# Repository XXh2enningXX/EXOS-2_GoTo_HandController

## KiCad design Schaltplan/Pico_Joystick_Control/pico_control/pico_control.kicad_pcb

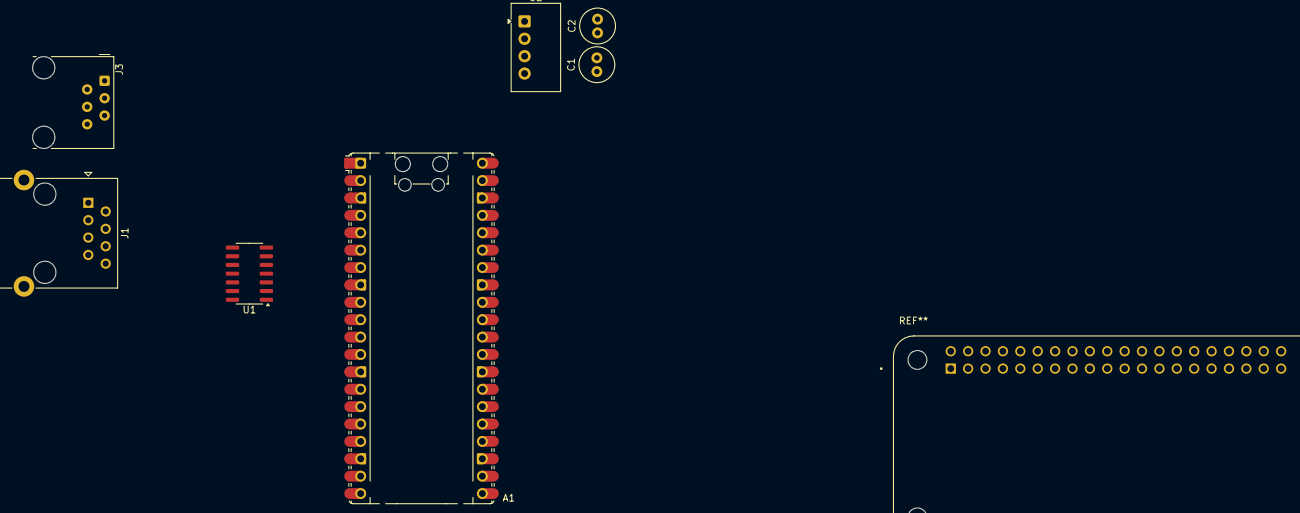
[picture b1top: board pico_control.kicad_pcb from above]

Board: 2 copper layers, 7 parts (0 on the bottom side), 15 nets, no tracks yet.

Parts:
A1: RaspberryPi_Pico; RaspberryPi_Pico_Common_Unspecified
C1, C2: C_Polarized; C_Radial_D5.0mm_H11.0mm_P2.00mm
J1: RJ45; RJ45_Ninigi_GE
J3: RJ12; RJ12_Amphenol_54601-x06_Horizontal
U1: TXB0104D; SOIC-14_3.9x8.7mm_P1.27mm
U2: TBA1-1211; Converter_DCDC_TRACO_TBA1-xxxx_THT

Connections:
+3.3V: A1.36 (3V3), U1.1 (VCCA)
+5V: A1.40 (VBUS), C1.1, U1.14 (VCCB), U2.4 (+Vout)
+12V: C2.1, J1.1, J1.2, U2.2 (+Vin)
GND: A1.3 (GND), A1.8 (GND), A1.13 (GND), A1.18 (GND), A1.23 (GND), A1.28 (GND), A1.38 (GND), C1.2, C2.2, J1.7, J1.8, U1.7 (GND), U2.1 (-Vin), U2.3 (-Vout)
unnamed: A1.35 (ADC_VREF), J3.1
unnamed: A1.33 (AGND), J3.5, J3.6
unnamed: A1.11 (GPIO8), U1.4 (A3)
unnamed: A1.12 (GPIO9), U1.3 (A2)
unnamed: A1.29 (GPIO22), J3.4
unnamed: A1.31 (GPIO26_ADC0), J3.2
unnamed: A1.32 (GPIO27_ADC1), J3.3
unnamed: J1.3, U1.13 (B1)
unnamed: J1.4, U1.12 (B2)
unnamed: J1.5, U1.11 (B3)
unnamed: J1.6, U1.10 (B4)

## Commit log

2025-04-17 Minimal Firmware, nur MNotorsteuerung und Tracking
2025-04-18 Menu angefangen. Muss noch Kompiliert werden und kann dann getestet werden.
2025-04-22 added manual for mount and flashing
2025-04-22 measurement of motor ctrl
2025-04-22 started lite controler version.
2025-04-23 included hex file
2025-04-23 still tryieng to compile
2025-04-23 für GPT
2025-04-23 FreeRTOS comiler works now
2025-04-24 work goes on
2025-04-24 found microcontroler on motor board, PIC16F690, Datasheet added
2025-04-24 started signal analyse
2025-04-25 Analyse der Motorsteuerung
2025-04-29 python signal check
2025-07-17 logic analyser files to csv
2025-07-17 fixed merg issues
2025-09-01 skyvision schematics angefangen
2025-09-01 skyvision board weitere verkabelung vermessen.
2025-09-01 started sorting out schematics
2025-09-01 marked pic pdf
2025-09-01 wip sortieren
2025-09-02 Schaltplan aufgeräumt
2025-09-03 repeated logic measurements
2025-09-03 experted LA Data as csv
2025-09-17 first pico firmware and HBX firmware for lookup
2025-09-19 Bilder
2025-09-19 pico FW mian
2025-09-29 code analyse
2025-09-29 new communication profile
2025-10-02 initial header for PIC, Joystick implemented, IT WORKS
2025-10-21 MS Antwort log
2025-10-24 evaluation of mount response
2026-04-04 rpi zero addad to scheme
